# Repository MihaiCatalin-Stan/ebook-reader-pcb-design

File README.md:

335CA Mihai-Catalin Stan
# OpenBook EBook Reader
This project contains the 2D and 3D Hardware design of an ebook reader, alongside the manufacturing files and some images of the product.
## Block Diagram

## Bill of Materials
|Component|Description|Buy Here|Datasheet|
|---------|-----------|--------|---------|
|ESP32_WROVER_EAGLE-LTSPICE_RR0402 | Resistor | https://eu.mouser.com/ProductDetail/Vishay-Beyschlag/MCS04020D9101BE000?qs=sGAEpiMZZMvdGkrng054twKDKoBh%252BscnK%2FuqkNk9X%252BqO%2Fz5%2F0u93Ow%3D%3D  | https://www.vishay.com/docs/28700/mcx0x0xpre.pdf
|EAGLE-LTSPICE_CC0402 | Capacitor | https://eu.mouser.com/ProductDetail/KEMET/C0402C475K8PACTU?qs=ulEaXIWI0c9ebKRT3r3htg%3D%3D | https://eu.mouser.com/datasheet/2/447/KEM_C1006_X5R_SMD-3316465.pdf
|ESP32C6_VARISTORCN1812 | Varistor | https://eu.mouser.com/ProductDetail/Schurter/PFMF.050.2?qs=1auRipcfynCums5v1iucSA%3D%3D | https://eu.mouser.com/datasheet/2/358/typ_PFMF-1275918.pdf
|CPH3225A | Capacitor | https://eu.mouser.com/ProductDetail/Seiko-Semiconductors/CPH3225A?qs=3etwrb1wR%252BhUOph6lAO7eg%3D%3D | https://eu.mouser.com/datasheet/2/360/Seiko_Instruments_MicroBattery_E_20230330_2024Jan_-3561061.pdf
|RCL_CPOL-EUCT3528 | Capacitor | https://eu.mouser.com/ProductDetail/Nichicon/LGN2W101MELA25?qs=Fe64Qgzkstf1zMszMsgRoA%3D%3D | https://eu.mouser.com/datasheet/2/293/e_lgn-3082370.pdf
|ADAFRUIT_LEDCHIP-LED0603 | LED | https://eu.mouser.com/ProductDetail/ams-OSRAM/KG-EELP41.22-PHRH-35-A8J8-20-R18?qs=ZcfC38r4Posajg8ZvCDQkg%3D%3D | https://eu.mouser.com/datasheet/2/588/KG_EELP41_22_EN-3572852.pdf
|ESP32_WROVER_SPARKFUN-DISCRETESEMI_MOSFET_PCH-DMG2305UX-7 | Transistor | https://eu.mouser.com/ProductDetail/Diodes-Incorporated/DMG2305UX-7?qs=L1DZKBg7t5F%2FNBHrjfxC%252Bg%3D%3D | https://www.diodes.com/assets/Datasheets/DMG2305UX.pdf
|SI1308EDL-T1-GE3 | Transistor | https://eu.mouser.com/ProductDetail/Vishay-Semiconductors/SI1308EDL-T1-GE3?qs=bX1%252BNvsK%2FBramh9tgpOaEw%3D%3D | https://www.vishay.com/docs/63399/si1308edl.pdf
| 744043680IND_4828-WE-TPC_WRE | Coil | https://eu.mouser.com/ProductDetail/Wurth-Elektronik/744043680?qs=PGXP4M47uW6VkZq%252BkzjrHA%3D%3D | https://www.we-online.com/components/products/datasheet/744043680.pdf
|112A-TAAR-R03_ATTEND | SD Card Mount | https://store.comet.srl.ro/Catalogue/Product/43497/ | https://store.comet.srl.ro/Catalogue/Product/43497/
|SAMACSYS_PARTS_USB4110-GF-A | USB Connector | https://eu.mouser.com/ProductDetail/GCT/USB4110-GF-A?qs=KUoIvG%2F9IlYiZvIXQjyJeA%3D%3D | https://eu.mouser.com/datasheet/2/837/GCT_USB4110_Product_Drawing___20k_cycles-3455479.pdf
|XC6220A331MR-G | LDO Voltage Regulator | https://eu.mouser.com/ProductDetail/Torex-Semiconductor/XC6220A331MR-G?qs=AsjdqWjXhJ8ZSWznL1J0gg%3D%3D | https://eu.mouser.com/datasheet/2/760/xc6220-3371556.pdf
|W25Q512JVEIQ | Flash Memory | https://eu.mouser.com/ProductDetail/Winbond/W25Q512JVEIQ?qs=l7cgNqFNU1jw6svr3at6tA%3D%3D | https://eu.mouser.com/datasheet/2/949/Winbond_W25Q512JV_Datasheet-3240039.pdf
|USBLC6-2SC6Y | ESD Protection | https://eu.mouser.com/ProductDetail/STMicroelectronics/USBLC6-2SC6Y?qs=gNDSiZmRJS%2FOgDexvXkdow%3D%3D | https://eu.mouser.com/datasheet/2/389/usblc6_2sc6y-1852505.pdf
|MCP73831 | Battery Controller | https://eu.mouser.com/ProductDetail/Microchip-Technology/MCP73831T-2ATI-MC?qs=yUQqVecv4qs9k7ug0bEXiw%3D%3D | https://eu.mouser.com/datasheet/2/268/MCP73831_Family_Data_Sheet_DS20001984H-3441711.pdf
|MAX17048G+T10 | Battery Management | https://eu.mouser.com/ProductDetail/Analog-Devices-Maxim-Integrated/MAX17048G%2bT10?qs=D7PJwyCwLAoGnnn8jEPRBQ%3D%3D | https://eu.mouser.com/datasheet/2/609/MAX17048_MAX17049-3469099.pdf
|FH34SRJ | E-Paper Display Header | https://eu.mouser.com/ProductDetail/Hirose-Connector/FH34SRJ-7S-0.5SH50?qs=vcbW%252B4%252BSTIqHa4IamMh36g%3D%3D | https://eu.mouser.com/datasheet/2/185/FH34SRJ_7S_0_5SH_50__CL0580_1200_0_50_2DDrawing_00-1615127.pdf
|ESP32_WROVER_AVX---SD0805S020S1R0_AVX_SD0805S020S1R0_0_0AVX_SD0805S020S1R0_0_0 | Diode | https://eu.mouser.com/ProductDetail/ROHM-Semiconductor/SCS310AMC7G?qs=iLKYxzqNS75xiccEgNnX2g%3D%3D | https://fscdn.rohm.com/en/products/databook/datasheet/discrete/sic/sbd/scs310am-e.pdf
|ESP32-C6-WROOM-1-N8 | MicroController | https://eu.mouser.com/ProductDetail/Espressif-Systems/ESP32-C6?qs=Imq1NPwxi75noDtUpuVuWw%3D%3D | https://eu.mouser.com/datasheet/2/891/esp32_c6_datasheet_en-3304070.pdf
|DS3231SN# | RTC Module | https://eu.mouser.com/ProductDetail/Analog-Devices-Maxim-Integrated/DS3231SN?qs=1eQvB6Dk1vhUlr8%2FOrV0Fw%3D%3D | https://eu.mouser.com/datasheet/2/609/DS3231-3421123.pdf
|ESP32_WROVER_BME680_BME680 | Integrated Environmental Unit | https://eu.mouser.com/ProductDetail/M5Stack/U001-C?qs=e8oIoAS2J1R2mB7ZY1%252BSZg%3D%3D | https://docs.m5stack.com/en/unit/envIII
| BD5229G-TR | Voltage Detector | https://eu.mouser.com/ProductDetail/ROHM-Semiconductor/BD5229G-TR?qs=sGAEpiMZZMutXGli8Ay4kAMqIQqqdOUlDFcDfPDPIK4%3D | https://fscdn.rohm.com/en/products/databook/datasheet/ic/power/voltage_detector/bd52xxg-e.pdf

## Hardware Details
* **MicroController - ESP32-C6-WROOM-1-N8:**
    * Pins are being used to communicate as follows:
        | Pin  | Signal       | Connected Component |
        |------|--------------|---------------------|
        | IO00 | INT_RTC      | RTC Module          |
        | IO01 | 32KHZ        | RTC Module          |
        | IO02 | MISO         | Flash, SD Card      |
        | IO03 | EPD_BUSY     | EPD                 |
        | IO04 | SS_SD        | SD Card             |
        | IO05 | EPD_DC       | EPD                 |
        | IO06 | SCK          | Flash, SD Card, BME688 |
        | IO07 | MOSI         | Flash, SD Card, EPD |
        | IO08 | GPIO8 / GND  | -                   |
        | IO09 | -            | -                   |
        | IO10 | EPD_CS       | EPD                 |
        | IO11 | FLASH_CS     | Flash               |
        | IO12 | USB_D-       | USB_C Connector     |
        | IO13 | USB_D+       | USB_C Connector     |
        | IO15 | IO/CHANGE    | Button              |
        | IO16 | TX           | -                   |
        | IO17 | RX           | -                   |
        | IO18 | RTC_RST      | RTC Module          |
        | IO19 | I2C_PW       | BME688              |
        | IO20 | EPD_3V3_C    | EPD                 |
        | IO21 | SDA          | RTC, BME688, Battery Level |
        | IO22 | SCL          | RTC, BME688, Battery Level |
        | IO23 | EPD_RST      | EPD                 |
    * The following Communication Protocols were used:
        | Protocol | Components |
        |----------|------------|
        | I2C      | RTC, BME688, Battery Level |
        | SPI      | Flash, SD Card, EPD |
        | USB      | USB_C Connector (Power) |
* **RTC Module:**
    * Communicates through `I2C` with the uC
        | Pin  | Signal       |
        |------|--------------|
        |Pin1| 32KHZ|
        |Pin3| INT_RTC|
        |Pin4| RTC_RST|
        |Pin14| VRTC|
        |Pin15| SDA|
        |Pin16| SCL|
* **Flash Module:**
    * Communicates through `SPI` with the uC and the other connected components
        | Pin  | Signal       |
        |------|--------------|
        |Pin1| FLASH_CS|
        |Pin2| MISO|
        |Pin5| MOSI|
        |Pin6| SCK|
* **SD Card Module:**
    * Communicates through `SPI` with the uC and the other connected components
        | Pin  | Signal       |
        |------|--------------|
        |P2| SS_SD|
        |P3| MOSI|
        |P5| SCK|
        |P7| MISO|
* **E-Paper Display:**
    * Communicates through `SPI` with the uC and the memory modules
        | Pin  | Signal       |
        |------|--------------|
        |Pin2| GDR|
        |Pin3| RESE|
        |Pin9| EPD_BUSY|
        |Pin10| EPD_RST|
        |Pin11| EPD_DC|
        |Pin12| EPD_CS|
        |Pin13| SCK|
        |Pin14| MOSI|
        |Pin15-16| EPD_3v3|
        |Pin21| PREVGH|
        |Pin23| PREVGL|
* **Battery Sensor:**
    * Checks the battery level and send data to the uC also with `I2C`
        | Pin  | Signal       |
        |------|--------------|
        |Pin2| VBAT|
        |Pin3| VBAT|
        |Pin7| SCL|
        |Pin8| SDA|
* **LDO - Voltage Regulator:**
    * Doesn't communicate with the uC but lowers the 5V to 3.3V for the uC and the attached modules
* **Environmental Sensor:**
    * Communicates through `I2C` with the uC and also with the RTC
        | Pin  | Signal       |
        |------|--------------|
        |Pin2| I2C_PW|
        |Pin3| SDA|
        |Pin4| SCL|
        |Pin6| I2C_PW|
        |Pin8| I2C_PW|
* **USB-C Connector:**
    * Power input for charging the battery
        | Pin  | Signal       |
        |------|--------------|
        |B4| VUSB|
        |B6| DP|
        |B7| DN|
        |B9| VUSB|
        |A4| VUSB|
        |A6| DP|
        |A7| DN|
        |A9| VUSB|
* **Buttons:**
    * Controls reset, boot and io/change signals by sending them to the uC when pressed

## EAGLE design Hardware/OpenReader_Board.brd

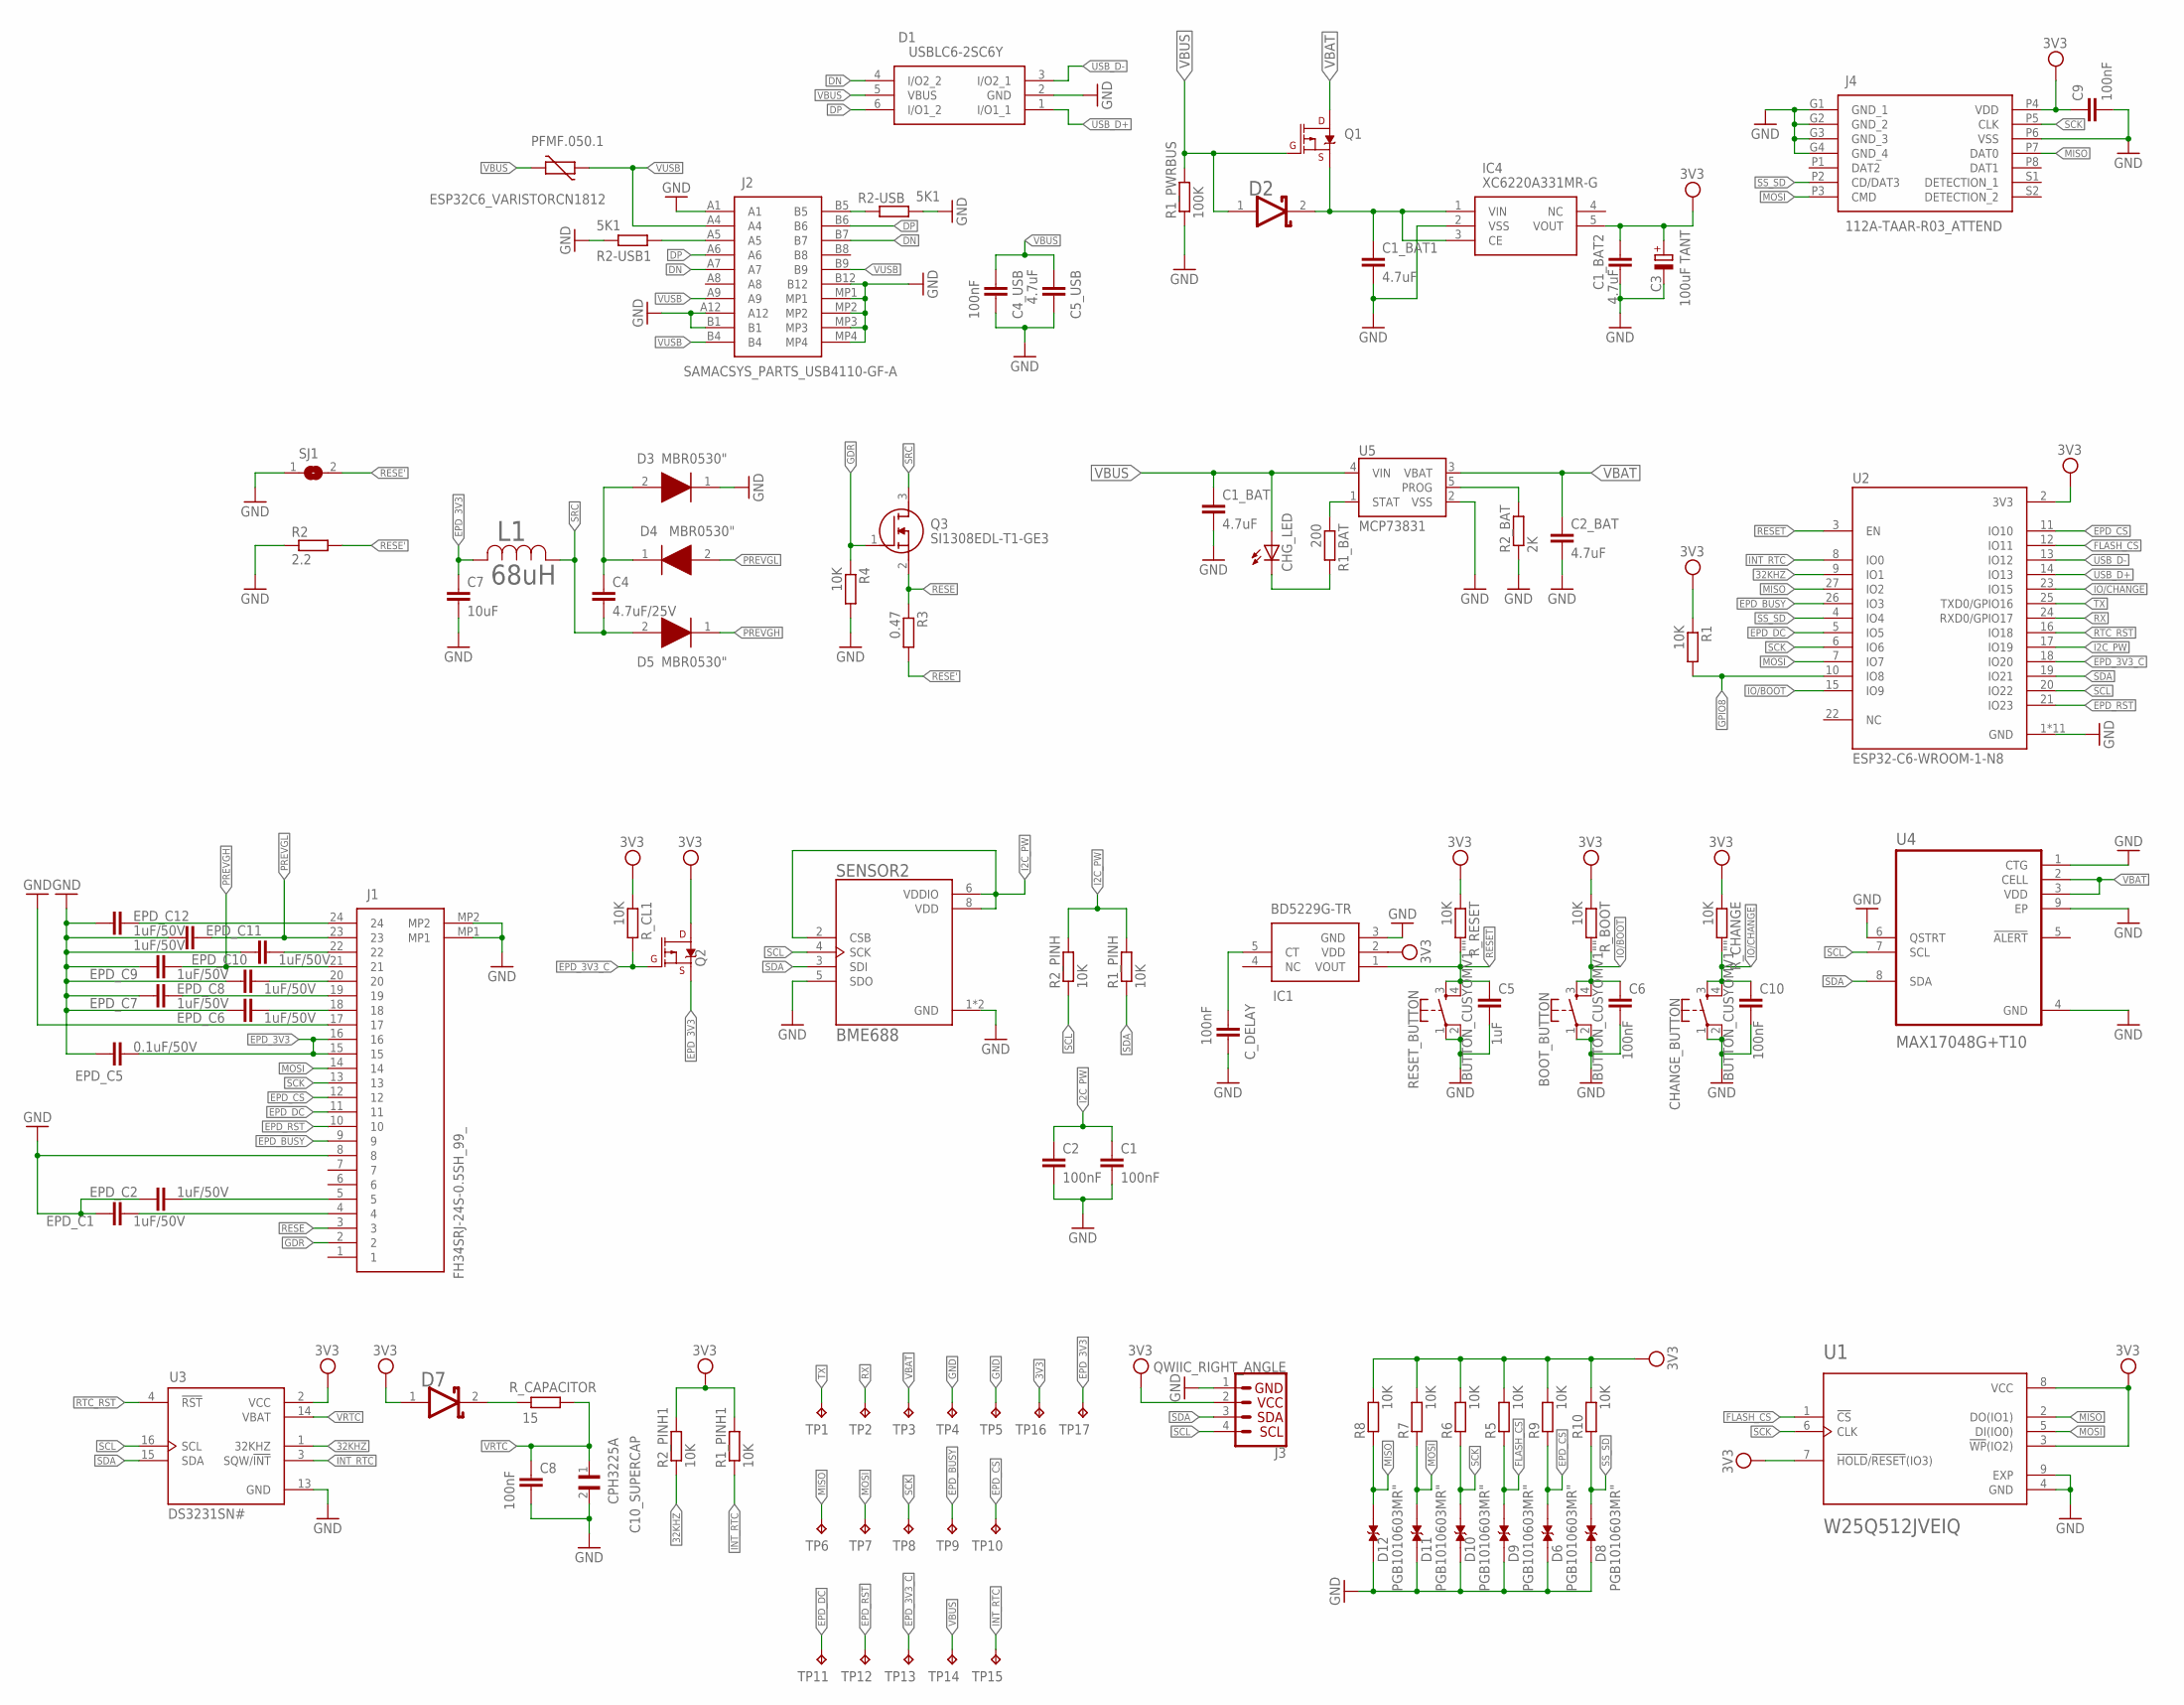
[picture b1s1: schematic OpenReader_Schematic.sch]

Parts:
BOOT_BUTTON: BUTTON_CUSYOMV1""; MYBUTTON
C1, C2, C4_USB, C6, C8, C9, C10: 100nF; EAGLE-LTSPICE_C0402
C1_BAT, C1_BAT1, C1_BAT2, C2_BAT, C5_USB: 4.7uF; EAGLE-LTSPICE_C0402
C3: 100uF TANT; RCL_CT3528
C4: 4.7uF/25V; EAGLE-LTSPICE_C0402
C5: 1uF; EAGLE-LTSPICE_C0402
C7: 10uF; EAGLE-LTSPICE_C0402
C10_SUPERCAP: CPH3225A; CAPCP3225X100N
CHANGE_BUTTON: BUTTON_CUSYOMV1""; MYBUTTON
CHG_LED: ADAFRUIT_LEDCHIP-LED0603; ADAFRUIT_CHIP-LED0603
C_DELAY: 100nF; EAGLE-LTSPICE_C0402
D1: USBLC6-2SC6Y; SOT95P280X145-6N
D2, D7: ESP32_WROVER_AVX---SD0805S020S1R0_AVX_SD0805S020S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; ESP32_WROVER_AVX---SD0805S020S1R0_AVX_SD0805S020S1R0_0
D3, D4, D5: MBR0530"; SOD3716X135N
D6, D8, D9, D10, D11, D12: PGB1010603MR"; DIOC1608X36N
EPD_C1, EPD_C2, EPD_C6, EPD_C7, EPD_C8, EPD_C9, EPD_C10, EPD_C11, EPD_C12: 1uF/50V; EAGLE-LTSPICE_C0402
EPD_C5: 0.1uF/50V; EAGLE-LTSPICE_C0402
IC1: BD5229G-TR; SOT95P280X125-5N
IC4: XC6220A331MR-G; SOT95P280X120-5N
J1: FH34SRJ-24S-0.5SH_99_; FH34SRJ24S05SH99
J2: SAMACSYS_PARTS_USB4110-GF-A; SAMACSYS_PARTS_USB4110GFA
J3: QWIIC_RIGHT_ANGLE; JST04_1MM_RA
J4: 112A-TAAR-R03_ATTEND; 112ATAARR03ATTEND
L1: 68uH; IND_4828-WE-TPC_WRE
PFMF.050.1: ESP32C6_VARISTORCN1812; ESP32C6_VARISTOR_CT/CN1812
Q1, Q2: 20V/4.2A/52mΩ/1.4W; ESP32_WROVER_SPARKFUN-DISCRETESEMI_SOT23-3
Q3: SI1308EDL-T1-GE3; SOT65P210X110-3N
R1, R1_PINH, R1_PINH1, R2_PINH, R2_PINH1, R4, R5, R6, R7, R8, R9, R10: 10K; ESP32_WROVER_EAGLE-LTSPICE_R0402
R1_BAT: 200; ESP32_WROVER_EAGLE-LTSPICE_R0402
R1_PWRBUS: 100K; ESP32_WROVER_EAGLE-LTSPICE_R0402
R2: 2.2; ESP32_WROVER_EAGLE-LTSPICE_R0402
R2-USB, R2-USB1: 5K1; ESP32_WROVER_EAGLE-LTSPICE_R0402
R2_BAT: 2K; ESP32_WROVER_EAGLE-LTSPICE_R0402
R3: 0.47; ESP32_WROVER_EAGLE-LTSPICE_R0402
RESET_BUTTON: BUTTON_CUSYOMV1""; MYBUTTON
R_BOOT: 10K; ESP32_WROVER_EAGLE-LTSPICE_R0402
R_CAPACITOR: 15; ESP32_WROVER_EAGLE-LTSPICE_R0402
R_CHANGE: 10K; ESP32_WROVER_EAGLE-LTSPICE_R0402
R_CL1: 10K; ESP32_WROVER_EAGLE-LTSPICE_R0402
R_RESET: 10K; ESP32_WROVER_EAGLE-LTSPICE_R0402
SENSOR2: BME688; ESP32_WROVER_BME680_PSON80P300X300X100-8N
SJ1: SJ
TP1, TP2, TP3, TP4, TP5, TP6, TP7, TP8, TP9, TP10, TP11, TP12, TP13, TP14, TP15, TP16, TP17: TPTP20R; TP20R
U1: W25Q512JVEIQ; SON127P600X800X80-9N
U2: ESP32-C6-WROOM-1-N8; XCVR_ESP32-C6-WROOM-1-N8
U3: DS3231SN#; SOIC127P1032X265-16N
U4: MAX17048G+T10; SON50P200X200X80-9N
U5: MCP73831; SOT23-5

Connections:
3V3: C1_BAT2.1, C3.+, C9.1, D7.1 (ANODE), IC1.2 (VDD), IC4.5 (VOUT), J3.2, J4.P4 (VDD), Q2.3 (D), R1.1, R1_PINH1.2, R2_PINH1.2, R5.2, R6.2, R7.2, R8.2, R9.2, R10.2, R_BOOT.1, R_CHANGE.1, R_CL1.1, R_RESET.1, TP16.TP, U1.3 (!WP!(IO2)), U1.7 (!HOLD!/!RESET!(IO3)), U1.8 (VCC), U2.2 (3V3), U3.2 (VCC)
32KHZ: R2_PINH1.1, U2.9 (IO1), U3.1 (32KHZ)
DN: D1.4 (I/O2_2), J2.A7, J2.B7
DP: D1.6 (I/O1_2), J2.A6, J2.B6
EPD_3V3: C7.1, EPD_C5.1, J1.15, J1.16, L1.2, Q2.2 (S), TP17.TP
EPD_3V3_C: Q2.1 (G), R_CL1.2, TP13.TP, U2.18 (IO20)
EPD_BUSY: J1.9, TP9.TP, U2.26 (IO3)
EPD_CS: D6.2, J1.12, R9.1, TP10.TP, U2.11 (IO10)
EPD_DC: J1.11, TP11.TP, U2.5 (IO5)
EPD_RST: J1.10, TP12.TP, U2.21 (IO23)
FLASH_CS: D9.2, R5.1, U1.1 (!CS), U2.12 (IO11)
GDR: J1.2, Q3.1 (G), R4.1
GND: BOOT_BUTTON.1, BOOT_BUTTON.2, C1.2, C1_BAT.2, C1_BAT1.2, C1_BAT2.2, C2.2, C2_BAT.2, C3.-, C4_USB.2, C5.2, C5_USB.2, C6.2, C7.2, C8.2, C9.2, C10.2, C10_SUPERCAP.2, CHANGE_BUTTON.1, CHANGE_BUTTON.2, C_DELAY.2, D1.2 (GND), D3.1 (K), D6.1, D8.1, D9.1, D10.1, D11.1, D12.1, EPD_C1.2, EPD_C2.2, EPD_C5.2, EPD_C6.2, EPD_C7.2, EPD_C8.2, EPD_C9.2, EPD_C10.2, EPD_C11.2, EPD_C12.2, IC1.3 (GND), IC4.2 (VSS), J1.8, J1.17, J1.MP1, J1.MP2, J2.A1, J2.A12, J2.B1, J2.B12, J2.MP1, J2.MP2, J2.MP3, J2.MP4, J3.1, J4.G1 (GND_1), J4.G2 (GND_2), J4.G3 (GND_3), J4.G4 (GND_4), J4.P6 (VSS), R1_PWRBUS.1, R2.1, R2-USB.2, R2-USB1.1, R2_BAT.1, R4.2, RESET_BUTTON.1, RESET_BUTTON.2, SENSOR2.1 (GND), SENSOR2.5 (SDO), SENSOR2.7 (GND), SJ1.1, TP4.TP, TP5.TP, U1.4 (GND), U1.9 (EXP), U2.1 (GND), U2.28 (GND), U2.29_1 (GND), U2.29_2 (GND), U2.29_3 (GND), U2.29_4 (GND), U2.29_5 (GND), U2.29_6 (GND), U2.29_7 (GND), U2.29_8 (GND), U2.29_9 (GND), U3.13 (GND), U4.1 (CTG), U4.4 (GND), U4.6 (QSTRT), U4.9 (EP), U5.2 (VSS)
GPIO8: R1.2, U2.10 (IO8)
I2C_PW: C1.1, C2.1, R1_PINH.2, R2_PINH.2, SENSOR2.2 (CSB), SENSOR2.6 (VDDIO), SENSOR2.8 (VDD), U2.17 (IO19)
INT_RTC: R1_PINH1.1, TP15.TP, U2.8 (IO0), U3.3 (SQW/!INT)
IO/BOOT: BOOT_BUTTON.3, BOOT_BUTTON.4, C6.1, R_BOOT.2, U2.15 (IO9)
IO/CHANGE: C10.1, CHANGE_BUTTON.3, CHANGE_BUTTON.4, R_CHANGE.2, U2.23 (IO15)
MISO: D12.2, J4.P7 (DAT0), R8.1, TP6.TP, U1.2 (DO(IO1)), U2.27 (IO2)
MOSI: D11.2, J1.14, J4.P3 (CMD), R7.1, TP7.TP, U1.5 (DI(IO0)), U2.7 (IO7)
unnamed: R1_BAT.1, U5.1 (STAT)
unnamed: CHG_LED.C, R1_BAT.2
unnamed: C1_BAT1.1, D2.2 (CATHODE), IC4.1 (VIN), IC4.3 (CE), Q1.2 (S)
unnamed: R2_BAT.2, U5.5 (PROG)
unnamed: J2.A5, R2-USB1.2
unnamed: C_DELAY.1, IC1.5 (CT)
unnamed: C4.1, D3.2 (A), D4.1 (K)
unnamed: EPD_C12.1, J1.24
unnamed: EPD_C10.1, J1.22
unnamed: EPD_C8.1, J1.20
unnamed: J2.B5, R2-USB.1
unnamed: EPD_C7.1, J1.19
unnamed: EPD_C6.1, J1.18
unnamed: EPD_C2.1, J1.5
unnamed: EPD_C1.1, J1.4
unnamed: D7.2 (CATHODE), R_CAPACITOR.2
PREVGH: D5.1 (K), EPD_C9.1, J1.21
PREVGL: D4.2 (A), EPD_C11.1, J1.23
RESE: J1.3, Q3.2 (S), R3.1
RESE': R2.2, R3.2, SJ1.2
RESET: C5.1, IC1.1 (VOUT), RESET_BUTTON.3, RESET_BUTTON.4, R_RESET.2, U2.3 (EN)
RTC_RST: U2.16 (IO18), U3.4 (!RST)
RX: TP2.TP, U2.24 (RXD0/GPIO17)
SCK: D10.2, J1.13, J4.P5 (CLK), R6.1, TP8.TP, U1.6 (CLK), U2.6 (IO6)
SCL: J3.4, R2_PINH.1, SENSOR2.4 (SCK), U2.20 (IO22), U3.16 (SCL), U4.7 (SCL)
SDA: J3.3, R1_PINH.1, SENSOR2.3 (SDI), U2.19 (IO21), U3.15 (SDA), U4.8 (SDA)
SRC: C4.2, D5.2 (A), L1.1, Q3.3 (D)
SS_SD: D8.2, J4.P2 (CD/DAT3), R10.1, U2.4 (IO4)
TX: TP1.TP, U2.25 (TXD0/GPIO16)
USB_D+: D1.1 (I/O1_1), U2.14 (IO13)
USB_D-: D1.3 (I/O2_1), U2.13 (IO12)
VBAT: C2_BAT.1, Q1.3 (D), TP3.TP, U4.2 (CELL), U4.3 (VDD), U5.3 (VBAT)
VBUS: C1_BAT.1, C4_USB.1, C5_USB.1, CHG_LED.A, D1.5 (VBUS), D2.1 (ANODE), PFMF.050.1.2, Q1.1 (G), R1_PWRBUS.2, TP14.TP, U5.4 (VIN)
VRTC: C8.1, C10_SUPERCAP.1, R_CAPACITOR.1, U3.14 (VBAT)
VUSB: J2.A4, J2.A9, J2.B4, J2.B9, PFMF.050.1.1

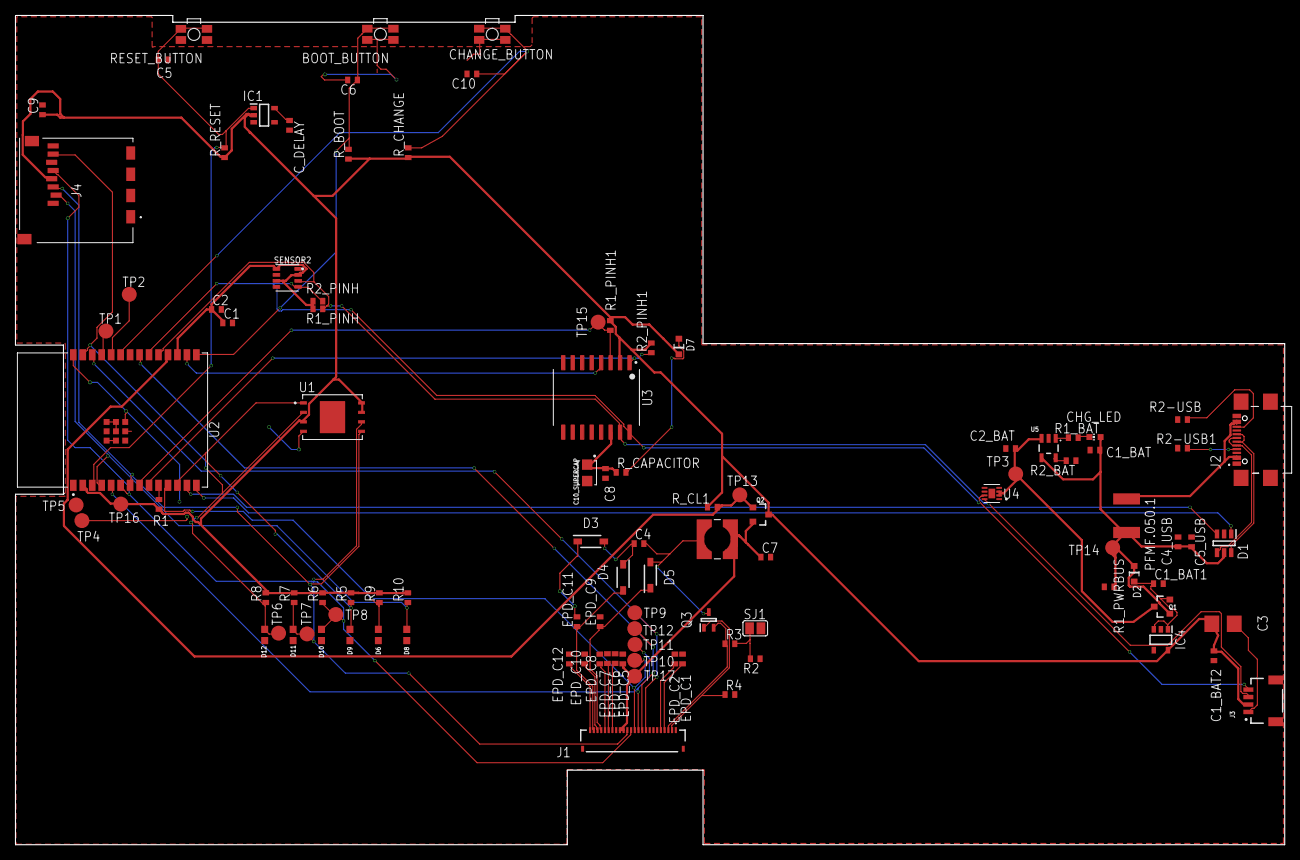
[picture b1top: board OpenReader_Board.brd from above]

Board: 2 copper layers, 170.2 x 111.2 mm, 103 parts (0 on the bottom side), 55 nets.

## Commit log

2025-04-05 Added Manufacturing, Mechanical and Hardware data for the project
    Added the schematic and pcb design for the project in the Hardware section.
    Added the manufacturing files such as gerbers, pick n place and bill of materials in the Manufacturing section.
    Added the 3D model of the whole product and the exploded view of it in the Mechanical section.
2025-04-06 Added Block Diagram to the images
2025-04-06 Added readme
    Added a readme containing data about the project, a block diagram, the BOM with all the required links and some general info about the hardware
2025-04-06 Added final product and components images
    Added images from the render view in fusion360 of the product and its independent components
2025-04-06 Updated README and added LICENSE
    Updated readme to contain data about the used pins and connected signals to each important component
2025-04-16 Fixed reported issues and aditionally modified battery design and gerbers archive
    - Fixed right angles
    - Filled GND plane empty patches
    - Created new and improved Display 3D design and battery 3D design
    - Modified the board's dimensions
    - Modified silkscreen to be more visible/readable

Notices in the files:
parts and their libraries:
SparkFun-IC-Power: Licensing: Creative Commons ShareAlike 4.0 International - https://creativecommons.org/licenses/by-sa/4.0
COPYRIGHT: Copyright (C) 2024 Ultra Librarian. All rights reserved.
